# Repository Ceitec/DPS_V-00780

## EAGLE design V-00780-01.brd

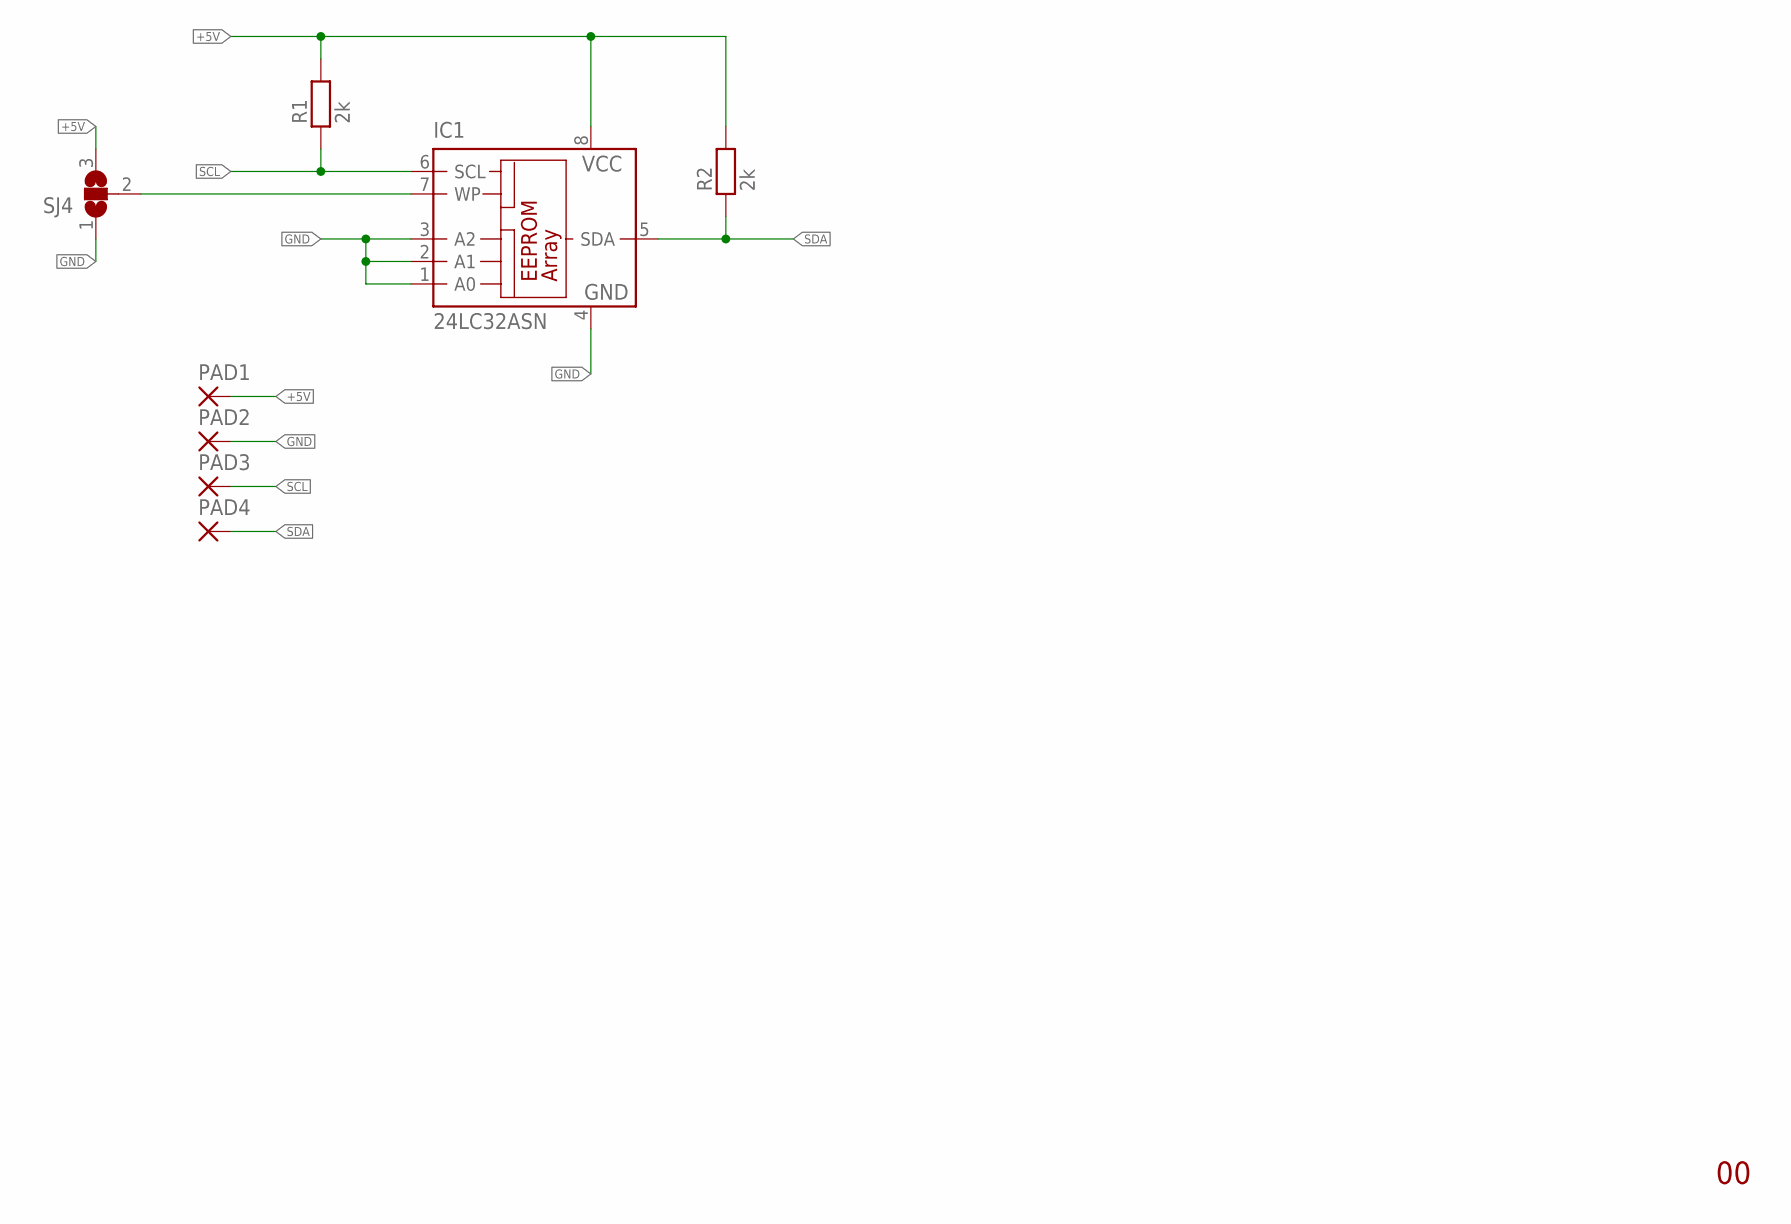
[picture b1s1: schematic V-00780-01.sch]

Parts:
IC1: 24LC32ASN; SO-08
PAD1, PAD2, PAD3, PAD4: SMD2; SMD1,27-2,54
R1, R2: 2k; 1206
SJ4: SJ2W; SJ_2

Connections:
+5V: IC1.8 (VCC), PAD1.1, R1.2, R2.2, SJ4.3
GND: IC1.1 (A0), IC1.2 (A1), IC1.3 (A2), IC1.4 (GND), PAD2.1, SJ4.1
SCL: IC1.6 (SCL), PAD3.1, R1.1
SDA: IC1.5 (SDA), PAD4.1, R2.1
WR_ENABLE: IC1.7 (WP), SJ4.2

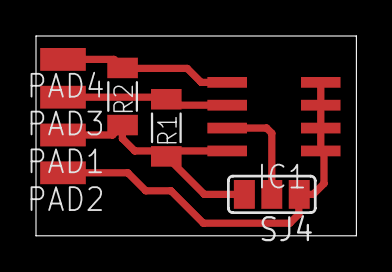
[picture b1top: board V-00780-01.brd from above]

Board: 2 copper layers, 17.8 x 11.1 mm, 8 parts (0 on the bottom side), 5 nets.

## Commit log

2016-02-10 :neckbeard: Added .gitattributes & .gitignore files
2016-02-10 v.1.0
    DPS k Joysticku - pomocná deska k tlačítkům a led diodám, encoder,
    displej a joystick

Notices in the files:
parts and their libraries:
Copyright (C) PaJa 2001-2014
